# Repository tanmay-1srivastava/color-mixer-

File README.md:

# color-mixer-
The repository contains the schematic of the circuit board developed on Eagle. Opamps and thermocouple are used to conrtol the intensity and wavelength of the LED.

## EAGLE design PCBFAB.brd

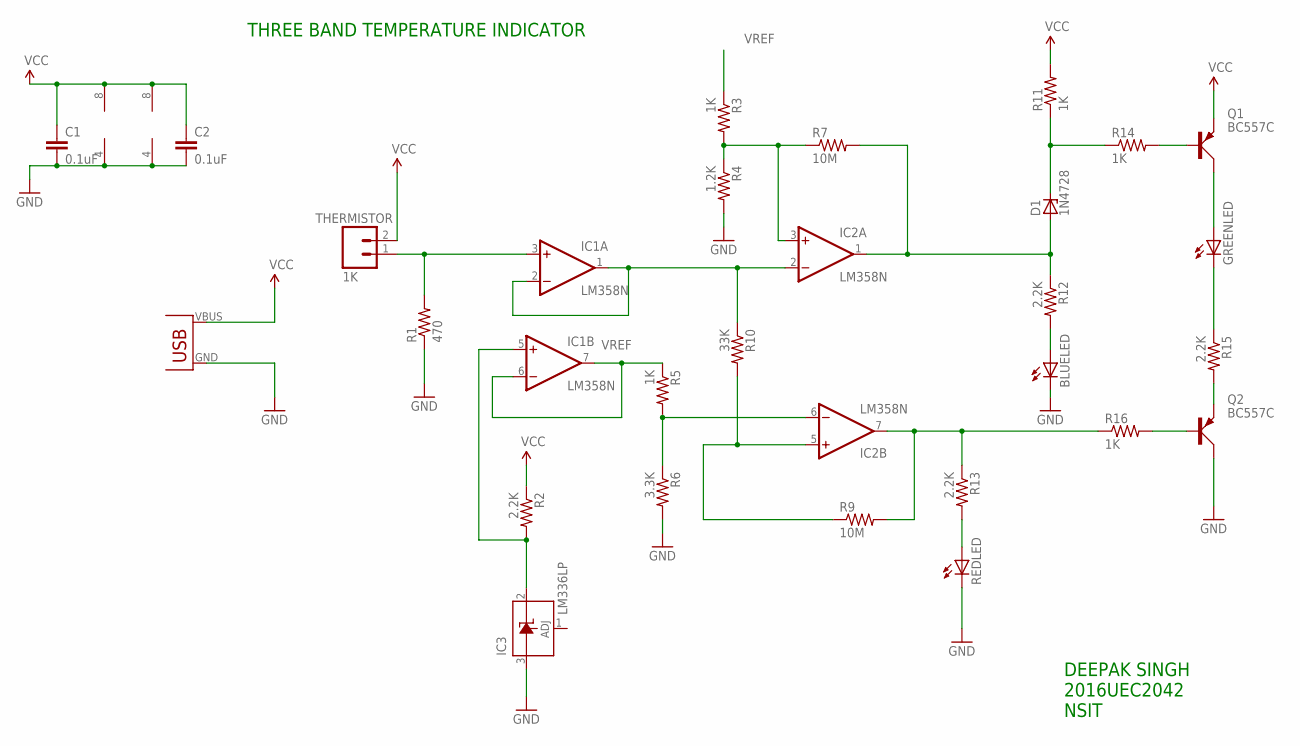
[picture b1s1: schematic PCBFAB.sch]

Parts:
BLUELED: LED5MM
C1, C2: 0.1uF; C025-024X044
D1: 1N4728; DO41Z10
GREENLED: LED5MM
IC1, IC2: LM358N; DIL08
IC3: LM336LP; TO92
Q1, Q2: BC557C; SOT54A
R1: 470; 0204/7
R2, R12, R13, R15: 2.2K; 0204/7
R3, R5, R11, R14, R16: 1K; 0204/7
R4: 1.2K; 0204/7
R6: 3.3K; 0204/7
R7, R9: 10M; 0204/7
R10: 33K; 0204/7
REDLED: LED5MM
THERMISTOR: 1K; 02P
U$1: USB(POWER)

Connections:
D: IC1.1 (OUT), IC1.2 (-IN), IC2.2 (-IN), R10.1
GND: BLUELED.K (C), C1.2, C2.2, IC1.4 (V-), IC2.4 (V-), IC3.3 (A), Q2.C, R1.1, R4.2, R6.2, REDLED.K (C), U$1.GND
unnamed: IC2.3 (+IN), R3.2, R4.1, R7.1
unnamed: IC2.5 (+IN), R9.1, R10.2
unnamed: IC1.5 (+IN), IC3.2 (C), R2.2
unnamed: IC1.3 (+IN), R1.2, THERMISTOR.1
unnamed: IC2.6 (-IN), R5.2, R6.1
unnamed: D1.A, IC2.1 (OUT), R7.2, R12.1
unnamed: IC2.7 (OUT), R9.2, R13.1, R16.1
unnamed: Q1.B, R14.2
unnamed: R13.2, REDLED.A
unnamed: BLUELED.A, R12.2
unnamed: D1.C, R11.1, R14.1
unnamed: Q2.B, R16.2
unnamed: GREENLED.A, Q1.C
unnamed: GREENLED.K (C), R15.1
unnamed: Q2.E, R15.2
VCC: C1.1, C2.1, IC1.8 (V+), IC2.8 (V+), Q1.E, R2.1, R11.2, THERMISTOR.2, U$1.VBUS (VCC)
VREF: IC1.6 (-IN), IC1.7 (OUT), R3.1, R5.1

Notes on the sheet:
DEEPAK SINGH 2016UEC2042 NSIT
THREE BAND TEMPERATURE INDICATOR

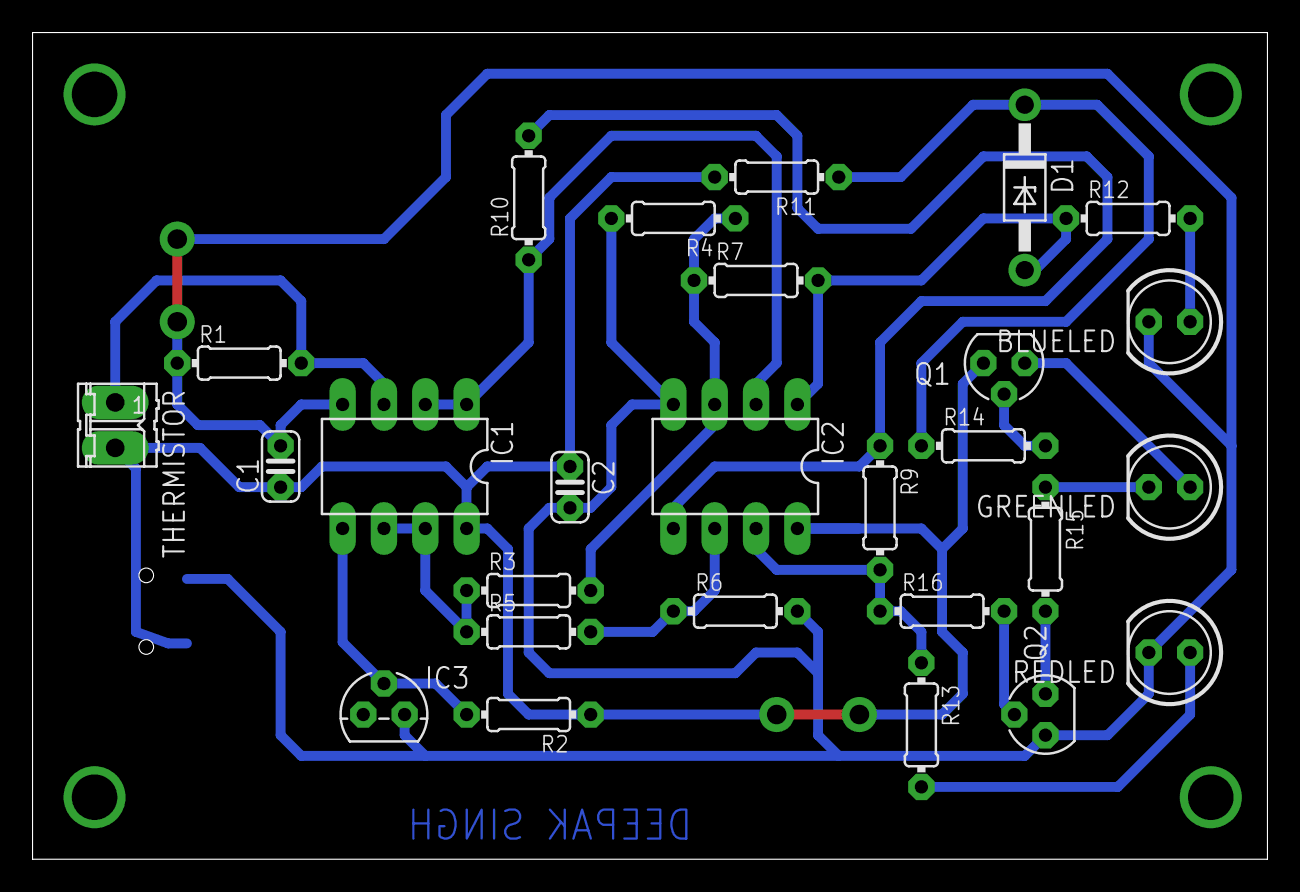
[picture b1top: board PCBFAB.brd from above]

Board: 2 copper layers, 75.9 x 50.8 mm, 28 parts (1 on the bottom side), 19 nets.
